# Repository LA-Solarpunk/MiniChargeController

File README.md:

# MiniChargeController

A small solar charge controller for single-cell lithium batteries, built around the TI BQ25792. It tracks the panel's maximum power point, charges either LiPo or LiFePO4, and runs a load at the same time it charges. Target cost is under $15 per unit in small quantities. 

**Status: schematic design. Not yet routed, not yet built, not yet tested. Do not fabricate from this repo.**

## Why this exists

Cheap all-in-one solar charger boards have no usable low-voltage cutoff and many don't have load path management. Boards that do have a healthy cutoff cost $20 and up, and most of those are sized for loads far bigger than ours. Charger ICs that do MPPT properly, like the CN3791, have no power path, so a load hanging off the battery corrupts charge termination and leaves the cell parked at 4.2V which will kill the lifetime of the cell. 

The BQ25798 covers all of it in one and we add a CH32V cheap RISC micro to handle setup, manual MPPT, low voltage cutoff, and charge source selection. It can be reprogrammed to support other chemistries as well like LiFePo4. The low power mode is 10uA coupled with the 24uA draw of the BQ25792 means potentially months of runtime when no solar is present.

## Requirements

- Solar input from 5V to 18V nominal panels, open-circuit voltage limited to 22V
- Charge a single-cell LiPo or LiFePO4 
- Maximum power point tracking
- Power a load while charging, without disturbing charge termination
- Configurable low-voltage cutoff that disconnects the load and leaves the battery to recover
- Raw battery voltage on the output, for a boost converter downstream
- USB-C as a secondary input, for bench charging or for running the device with no panel

### Charger

TI BQ25792, a buck-boost charger with four integrated switching FETs, an integrated BATFET, current sensing, and NVDC power path management. Input range is 3.6V to 24V with a 30V absolute maximum. MPPT works by periodically halting the converter, measuring panel open-circuit voltage, and setting the input voltage regulation point to a configurable fraction of it. The BQ25798 has builtin MPPT, but is more expensive so this saves a buck because we already have an MCU.

Power path means the system rail is regulated separately from the battery, so load current does not flow through the charge termination sense path. The load runs off SYS, the cell charges independently, and neither interferes with the other.

### Inputs

Solar arrives on VAC2, USB-C on VAC1. Each input has its own pair of back-to-back N-channel FETs driven from the charger's ACDRV pins, so the charger selects which source feeds the converter. Back-to-back is required because a single FET's body diode conducts regardless of gate state, and the mux has to block in both directions.

Solar input has reverse polarity protection: a P-channel FET with its drain at the connector and source at VAC2, gate pulled to ground through 100k. A 10V zener clamps gate-to-source, since a 22V panel would otherwise exceed the FET's 12V gate rating. Normal polarity forward-biases the body diode, the channel enhances, and the drop collapses to a few millivolts. Reversed polarity leaves the gate at zero and nothing conducts.

The MCU selects the input, so the current plan is to use USB when no solar is present and the battery is below some threshold so that USB can be used as a backup power supply if desired.

### Microcontroller

A CH32V003J4M6 in SOP-8, powered from SYS, configures the charger over I2C at power-on and then sleeps. It is required rather than optional, because several things the design depends on are off by default:

- MPPT doesn't work on this chip, but we can fake it with some simple logic
- Input source selection is host-controlled
- The I2C watchdog reverts every register to its power-on default when it expires, so it has to be turned off
- The power-on charge voltage is 4.2V per cell from the PROG resistor, which overcharges a LiFePO4 cell
- The MCU shuts off load power when under voltage

`CE` is held high by a pull-up out of reset, so charging stays off until the MCU has written the configuration registers and read them back. This helps ensure the MCU is functioning before charging begins.

### Low voltage cutoff

The working cutoff runs in firmware. The CH32V003's programmable voltage detector raises an interrupt at a threshold set in software, the handler opens the load switch, and the part sleeps. The MCU wakes on the charger's interrupt line when an input source appears, or on a long timer, and reads battery voltage with the load still disconnected before closing the switch again. 

The independent watchdog covers firmware that hangs while the cell is still healthy.

### Battery temperature

There's a thermistor on the board for thermal cutoff, but there's a PCB jumper that can be cut and an external or battery thermistor can be used.

Fitting the thermistor is recommended for outdoor deployment. This can help prevent thermal runaway especially when operating outdoors in hot/sunny weather.

### Input current limit

The ILIM_HIZ pin is voltage-programmed. It becomes a hard ceiling that the host cannot program past. It's currently set to support up to 3A.

The ceiling also matters because the reverse-protection FET is a 50mΩ SOT-23 part. At 5A it would dissipate 1.25W which is a lot of losses for panels that will probably be in the 5W-10W range. Practical input ceiling for this board is set by that FET rather than by the charger.

## Cost

This board is built with jlcpcb parts and mfg in mind, currently around $10 per unit at volume 50. The charger IC is about $2 of that. Most of the rest is the four-layer board, assembly, the inductor, the connectors, and thirteen bulk capacitors.

## Known issues

## Hardware notes

## Repository layout

```
MiniChargeController/     KiCad project
```

## Toolchain

- KiCad 10 for schematic and layout
- ch32fun for firmware, once firmware exists

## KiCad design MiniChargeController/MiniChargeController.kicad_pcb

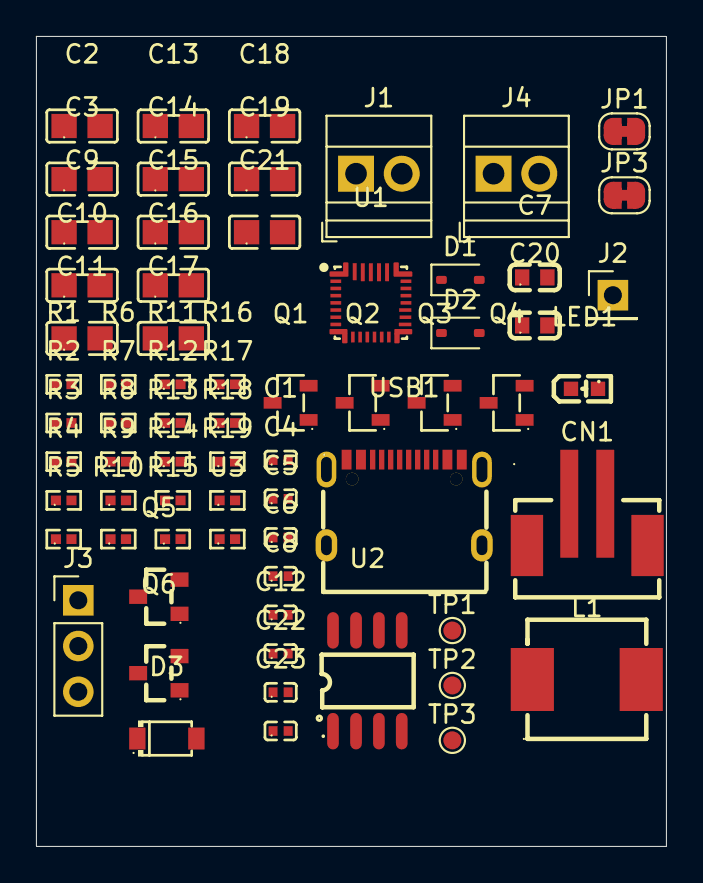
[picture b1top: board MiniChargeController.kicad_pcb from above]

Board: 2 copper layers, 35.0 x 45.0 mm, 67 parts (0 on the bottom side), 41 nets, no tracks yet.

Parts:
C1, C4, C5, C8, C22: 0.1u; C1525_C0402
C2, C3, C9, C10, C11, C13, C14, C15, C16, C17, C18, C19, C21: 10u; C440198_C0805
C6: 4.7u; C23733_C0402
C7, C20: 47n; C1622_C0603
C12: 1n; C1523_C0402
C23: 10n; C15195_C0402
CN1: B2B-PH-SM4-TB (LF)(SN); C160352_CONN-SMD_B2B-PH-SM4-TB-LF-SN
D1, D2: D_Zener; D_SOD-323
D3: 10V; C19077408_SOD-123_L2_7-W1_6-LS3_7-RD
J1, J4: Screw_Terminal_01x02; TerminalBlock_Xinya_XY308-2.54-2P_1x02_P2.54mm_Horizontal
J2: Conn_01x01; PinHeader_1x01_P2.54mm_Vertical
J3: Conn_01x03; PinHeader_1x03_P2.54mm_Vertical
JP1, JP3: SolderJumper-2_P1.3mm_Bridged_RoundedPad1.0x1.5mm
L1: 2.2u; C49190166_IND-SMD_L7_0-W6_6_XR0624
LED1: RED_LED; C2286_LED-SMD_L1_6-W0_8-R-RD
Q1, Q2, Q3, Q4: AO3400A; C20917_SOT-23-3_L2_9-W1_3-P1_90-LS2_4-BR
Q5, Q6: AO3401A; C15127_SOT-23_L2_9-W1_3-P1_90-LS2_4-BR
R1, R5: 5.1k; C25905_R0402
R2: 2.2k; C25879_R0402
R3, R4: 294; C2986591_R0402
R6, R12, R15, R17, R19: 100k; C25741_R0402
R7: 100; C25076_R0402
R8: 5.23k; C2933105_R0402
R9: 30.1k; C29402_R0402
R10: 147k; C163489_R0402
R11, R13, R14: 4.7k; C25900_R0402
R16: 1M; C26083_R0402
R18: 10k; C25744_R0402
TP1, TP2, TP3: TestPoint; TestPoint_Pad_D1.0mm
U1: BQ25798RQMR; C2876593_QFN-29_L4_0-W4_0-P0_40-TL-BQ25792RQMR
U2: CH32V003J4M6_C5346354; C5346354_SOP-8_L4_9-W3_8-P1_27-LS6_0-BL
U3: 10k; C5121989_R0402
USB1: TYPE-C 16PIN 2MD(073); C2765186_USB-C-SMD_TYPE-C-16PIN-2MD-073

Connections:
/ACDRV1: R4.2, U1.11 (ACDRV1)
/ACDRV2: R3.2, U1.10 (ACDRV2)
/CE: R15.1, U1.13 (CE#), U2.1 (PD6/A6/OSCI)
/ILIM_HIZ: R10.1, R12.2, U1.17 (ILIM_HIZ)
/INT#: R18.1, R19.2, U1.21 (INT#)
/PWR_CTL: R17.2, U2.7 (PC4/A2)
/SCl: R13.1, TP2.1 (1_1), U1.14 (SCL), U2.6 (PC2/SCL)
/SDA: R14.1, TP3.1 (1_1), U1.15 (SDA), U2.5 (PC1/SDA)
/SW1: C7.1, L1.1, U1.28 (SW1)
/SW2: C20.1, L1.2, U1.26 (SW2)
/TS: J2.1 (Pin_1_1), JP1.2 (B), R8.1, R9.2, U1.16 (TS)
/VAC1: C5.2, Q3.3 (D), U1.9 (VAC1), USB1.A4B9 (VBUS), USB1.B4A9 (VBUS)
/VAC2: D3.1 (K), Q2.3 (D), Q5.2 (S), U1.8 (VAC2)
GND: C1.1, C2.1, C3.1, C4.1, C5.1, C6.2, C8.1, C9.1, C10.1, C11.1, C12.1, C13.1, C14.1, C15.1, C16.1, C17.1, C18.1, C19.1, C21.1, C22.1, C23.1, CN1.2, CN1.3, CN1.4, J1.1, J3.3, J4.2, R1.2, R5.2, R6.1, R9.1, R11.2, R12.1, U1.27 (GND), U2.2 (VSS), U3.1, USB1.13 (EH), USB1.14 (EH), USB1.A1B12 (GND), USB1.B1A12 (GND)
unnamed: D1.2 (A), Q1.2 (S), Q2.2 (S)
unnamed: D1.1 (K), Q1.1 (G), Q2.1 (G), R3.1
unnamed: D2.2 (A), Q3.2 (S), Q4.2 (S)
unnamed: D2.1 (K), Q3.1 (G), Q4.1 (G), R4.1
unnamed: D3.2 (A), Q5.1 (G), R6.2
unnamed: C4.2, J1.2, Q5.3 (D)
unnamed: J3.2, U2.8 (PD4/A7)
unnamed: J4.1, Q6.3 (D)
unnamed: JP1.1 (A), U3.2
unnamed: JP3.2 (B), R15.2
unnamed: LED1.1 (A), R2.2
unnamed: LED1.2 (K), U1.1 (STAT)
unnamed: C23.2, Q6.1 (G), R16.1, R17.1
unnamed: R7.1, U1.18 (BATP)
unnamed: C7.2, U1.4 (BTST1)
unnamed: C20.2, U1.19 (BTST2)
unnamed: R11.1, U1.20 (PROG)
unnamed: TP1.1 (1_1), U1.12 (QON#)
unnamed: C12.2, U1.24 (SDRV)
unnamed: R18.2, U2.3 (PA2/OSCO/A0)
unnamed: R5.1, USB1.A5 (CC1)
unnamed: R1.1, USB1.B5 (CC2)
VBAT: C18.2, C19.2, CN1.1, R7.2, U1.22 (BAT), U1.23 (BAT)
VBUS: C1.2, C2.2, C3.2, Q1.3 (D), Q4.3 (D), U1.2 (VBUS), U1.3 (VBUS)
VCC: C13.2, C14.2, C15.2, C16.2, C17.2, C21.2, C22.2, J3.1, JP3.1 (A), Q6.2 (S), R13.2, R14.2, R16.2, R19.1, U1.25 (SYS), U2.4 (VDD)
VPMID: C8.2, C9.2, C10.2, C11.2, U1.29 (PMID)
VREGN: C6.1, R2.1, R8.2, R10.2, U1.5 (REGN)
